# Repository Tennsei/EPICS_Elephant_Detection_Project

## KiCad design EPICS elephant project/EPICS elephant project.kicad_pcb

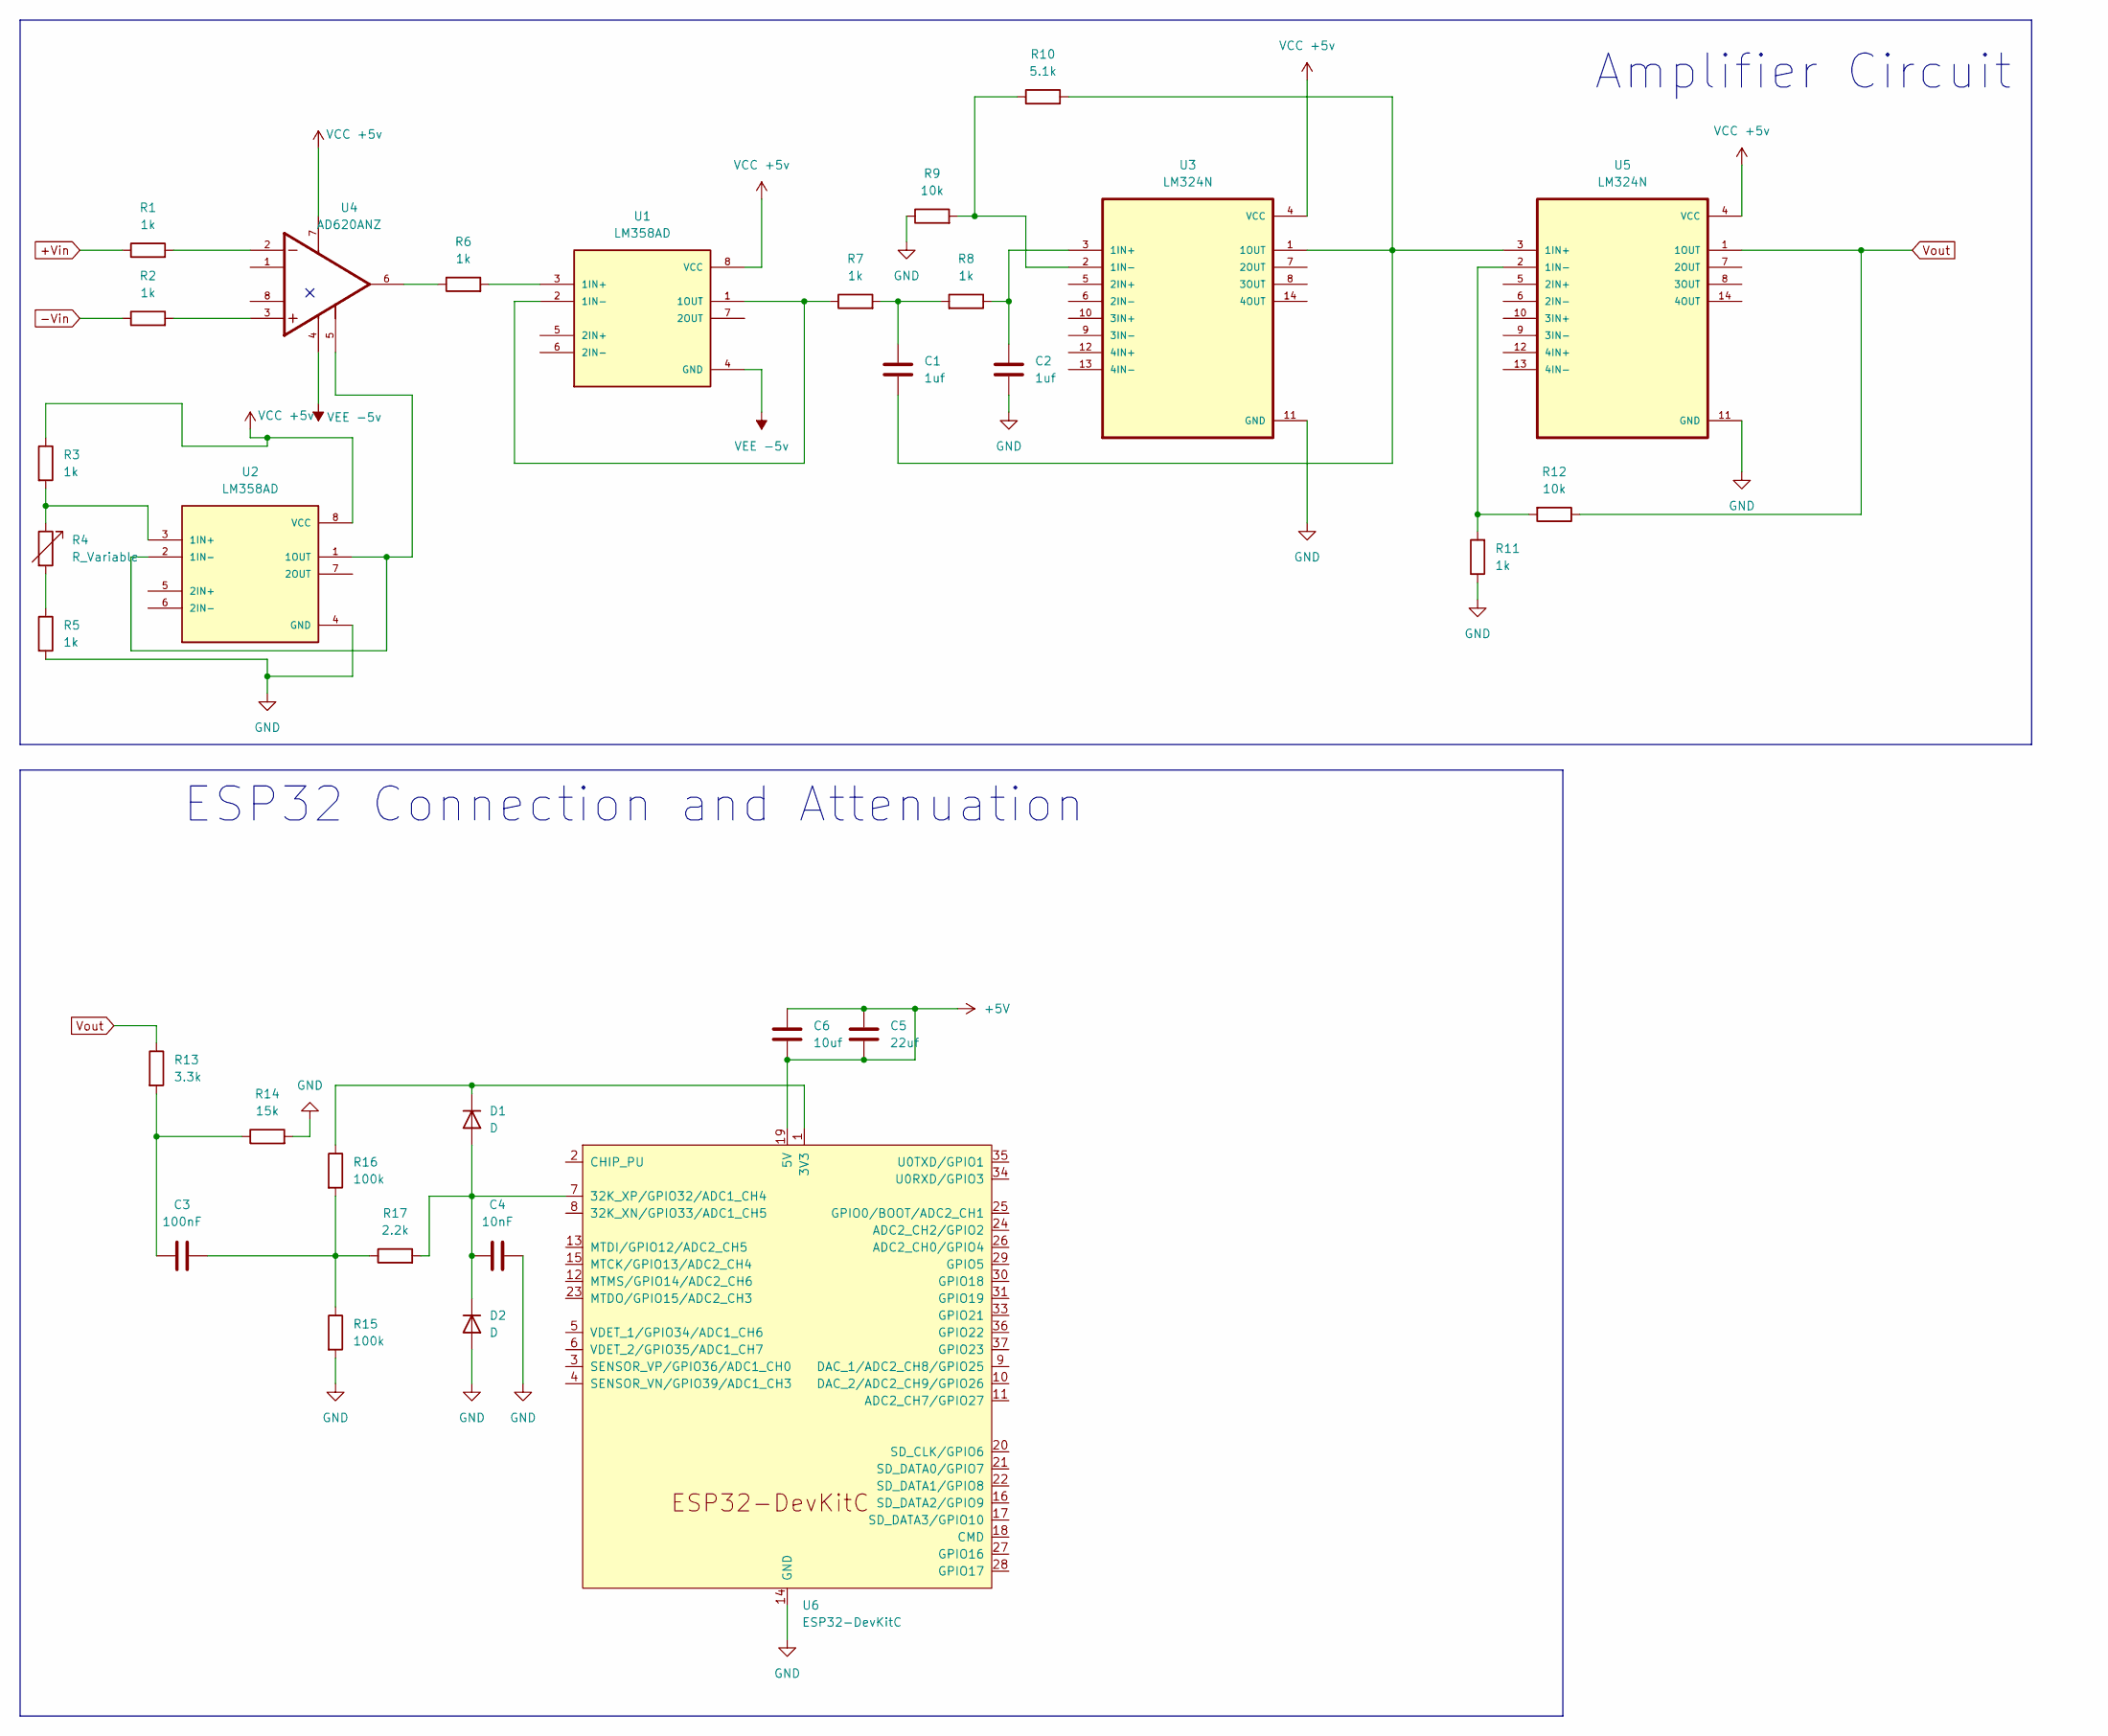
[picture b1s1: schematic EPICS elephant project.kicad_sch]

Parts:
C1, C2: 1uf; CP_Radial_D5.0mm_P2.00mm
C3: 100nF; CP_Radial_D5.0mm_P2.00mm
C4: 10nF; CP_Radial_D5.0mm_P2.00mm
C5: 22uf; CP_Radial_D5.0mm_P2.00mm
C6: 10uf; CP_Radial_D5.0mm_P2.00mm
D1, D2: D; D_1206_3216Metric_Pad1.42x1.75mm_HandSolder
R1, R2, R3, R5, R6, R7, R8, R11: 1k; R_Axial_DIN0204_L3.6mm_D1.6mm_P7.62mm_Horizontal
R4: R_Variable; R_Axial_DIN0204_L3.6mm_D1.6mm_P7.62mm_Horizontal
R9, R12: 10k; R_Axial_DIN0204_L3.6mm_D1.6mm_P7.62mm_Horizontal
R10: 5.1k; R_Axial_DIN0204_L3.6mm_D1.6mm_P7.62mm_Horizontal
R13: 3.3k; R_Axial_DIN0204_L3.6mm_D1.6mm_P7.62mm_Horizontal
R14: 15k; R_Axial_DIN0204_L3.6mm_D1.6mm_P7.62mm_Horizontal
R15, R16: 100k; R_Axial_DIN0204_L3.6mm_D1.6mm_P7.62mm_Horizontal
R17: 2.2k; R_Axial_DIN0204_L3.6mm_D1.6mm_P7.62mm_Horizontal
U1, U2: LM358AD; SOIC127P600X175-8N
U3, U5: LM324N; DIP794W45P254L1969H508Q14
U4: AD620ANZ; DIP787W46P254L1016H533Q8; PARTREV H
U6: ESP32-DevKitC

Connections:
+5V: C5.1, C5.2, C6.1, C6.2, U6.19 (5V)
+Vin: R1.1
-Vin: R2.1
GND: C2.2, C4.1, D2.2 (A), R5.2, R9.1, R11.1, R14.2, R15.2, U2.4 (GND), U3.11 (GND), U5.11 (GND), U6.14 (GND), U6.32 (GND), U6.38 (GND)
unnamed: C1.1, R7.2, R8.2
unnamed: C3.1, R13.2, R14.1
unnamed: C3.2, R15.1, R16.2, R17.1
unnamed: C4.2, D1.2 (A), D2.1 (K), R17.2, U6.7 (32K_XP/GPIO32/ADC1_CH4)
unnamed: D1.1 (K), R16.1, U6.1 (3V3)
unnamed: R1.2, U4.2
unnamed: R2.2, U4.3
unnamed: R4.2, R5.1
unnamed: R6.1, U4.6
unnamed: R6.2, U1.3 (1IN+)
unnamed: R7.1, U1.1 (1OUT), U1.2 (1IN-)
unnamed: R3.2, R4.1, U2.3 (1IN+)
unnamed: U2.1 (1OUT), U2.2 (1IN-), U4.5
unnamed: C2.1, R8.1, U3.3 (1IN+)
unnamed: R9.2, R10.1, U3.2 (1IN-)
unnamed: C1.2, R10.2, U3.1 (1OUT), U5.3 (1IN+)
unnamed: R11.2, R12.2, U5.2 (1IN-)
VCC +5v: R3.1, U1.8 (VCC), U2.8 (VCC), U3.4 (VCC), U4.7, U5.4 (VCC)
VEE -5v: U1.4 (GND), U4.4
Vout: R12.1, R13.1, U5.1 (1OUT)

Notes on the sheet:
Amplifier Circuit
ESP32 Connection and Attenuation

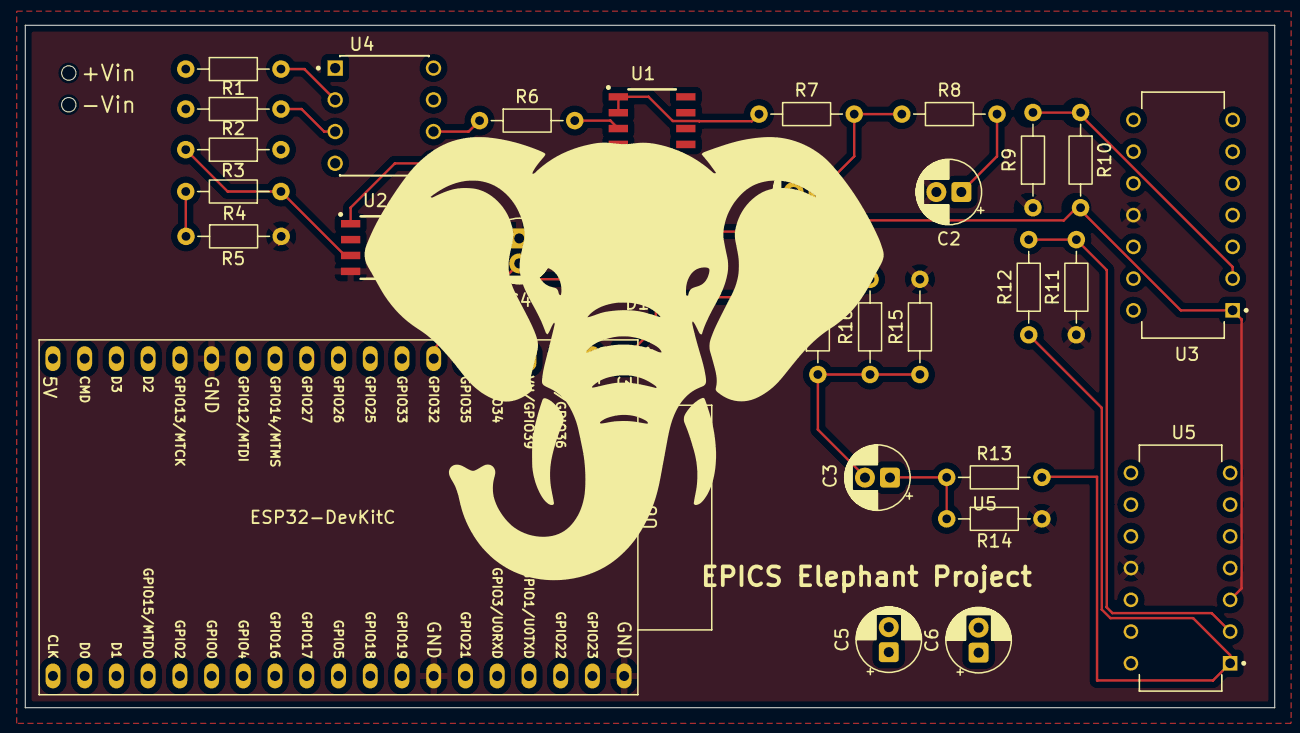
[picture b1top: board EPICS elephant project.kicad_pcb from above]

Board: 2 copper layers, 100.0 x 54.6 mm, 32 parts (0 on the bottom side), 22 nets.

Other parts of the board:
-Vin: (no value)

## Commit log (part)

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2026-02-25 Base stuff
2026-02-25 Adding the amplifiers for the circuit
2026-03-03 Schematic wiring
2026-03-03 Fixing simulation things
2026-03-03 Added the exact components we need to use, also added an attenuation circuit step down from 5v to 3.3v for the ESP32 ADC read outs
2026-03-03 tried to figure out how to simulate it
    didnt work lots of errors
2026-03-04 Added decoupling circuit for ESP32
2026-03-04 simulating the circuit with default spice opamps
2026-03-04 trying to fix the circuit
2026-03-05 Getting the simulation to work
2026-03-05 changed the frequency, added the attenuation circuit and expirementing on that
2026-03-14 Created the PCB, still need to make changes depending on testing on breadboard
